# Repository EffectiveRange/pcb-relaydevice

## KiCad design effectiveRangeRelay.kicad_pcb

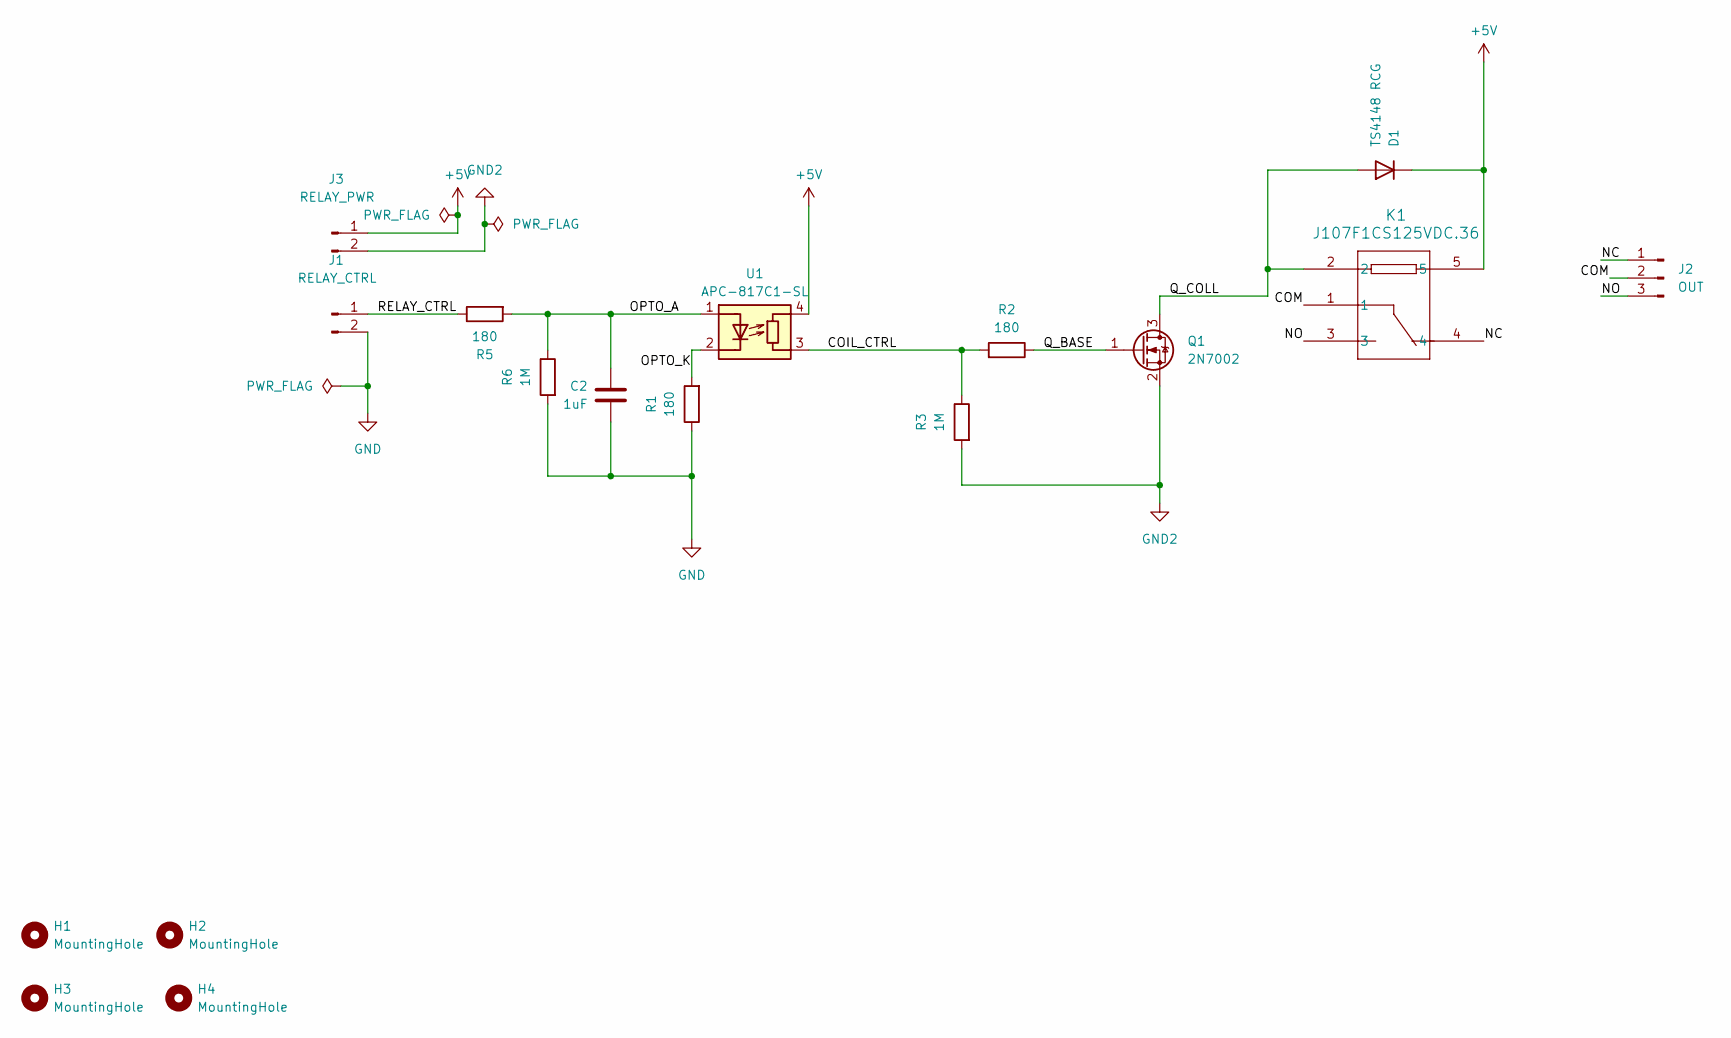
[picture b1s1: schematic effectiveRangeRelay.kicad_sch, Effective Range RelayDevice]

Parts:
C2: 1uF; C_0603_1608Metric_Pad1.08x0.95mm_HandSolder; MPN GRM188R61A105KA61D
D1: TS4148 RCG; D_0603_1608Metric; MPN TS4148 RCG
H1, H2, H3, H4: MountingHole; MountingHole_2.7mm_M2.5_DIN965
J1: RELAY_CTRL; PinHeader_1x02_P2.54mm_Vertical; MPN 61300211121
J2: OUT; CONN_1935174_PXC; MPN 1935174
J3: RELAY_PWR; PinHeader_1x02_P2.54mm_Vertical; MPN 61300211121
K1: J107F1CS125VDC.36; RELAY5_J107F-1C_CRS; MPN J107F1CS125VDC.36
Q1: 2N7002; SOT-23; MPN 2N7002
R1, R2, R5: 180; R_0603_1608Metric; MPN ERJ-PA3F1800V
R3, R6: 1M; R_0603_1608Metric; MPN ERJ-PA3J105V
U1: APC-817C1-SL; MPN APC-817C1-SL

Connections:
+5V: D1.1 (K), J3.1, K1.5, U1.4 (R)
/COIL_CTRL: R2.2, R3.1, U1.3 (R)
/COM: J2.2, K1.1
/NC: J2.1, K1.4
/NO: J2.3, K1.3
/OPTO_A: C2.1, R5.2, R6.1, U1.1 (A)
/OPTO_K: R1.2, U1.2 (K)
/Q_BASE: Q1.1 (G), R2.1
/Q_COLL: D1.2 (A), K1.2, Q1.3 (D)
/RELAY_CTRL: J1.1, R5.1
GND: C2.2, J1.2, R1.1, R6.2
GND2: J3.2, Q1.2 (S), R3.2

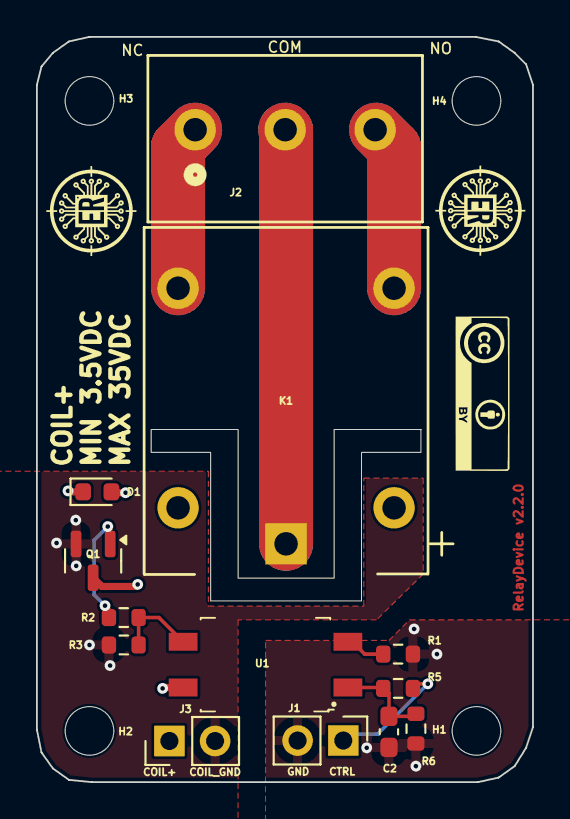
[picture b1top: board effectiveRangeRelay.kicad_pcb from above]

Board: 4 copper layers, 27.6 x 41.4 mm, 17 parts (0 on the bottom side), 12 nets.

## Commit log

2024-06-17 Bumping release from 2.1.0 to 2.2.0

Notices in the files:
effectiveRangeRelay.kicad_pcb:
visit https://creativecommons.org/licenses/by/4.0
is licensed under CC BY 4.0. To view a copy of this license,
License: MrHAT © 2024 by Ferenc Nandor Janky & Attila Gombos
